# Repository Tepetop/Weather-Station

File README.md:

# Stacja pogodowa

Coś tu dopisze jeszcze

## AI coding harness

Lokalny agent Python do analizy i edycji kodu STM32, z automatyczną kompilacją
trzech wariantów projektu i testami hosta.

Instrukcja instalacji i przykłady: [tools/ai_harness/README.md](tools/ai_harness/README.md).

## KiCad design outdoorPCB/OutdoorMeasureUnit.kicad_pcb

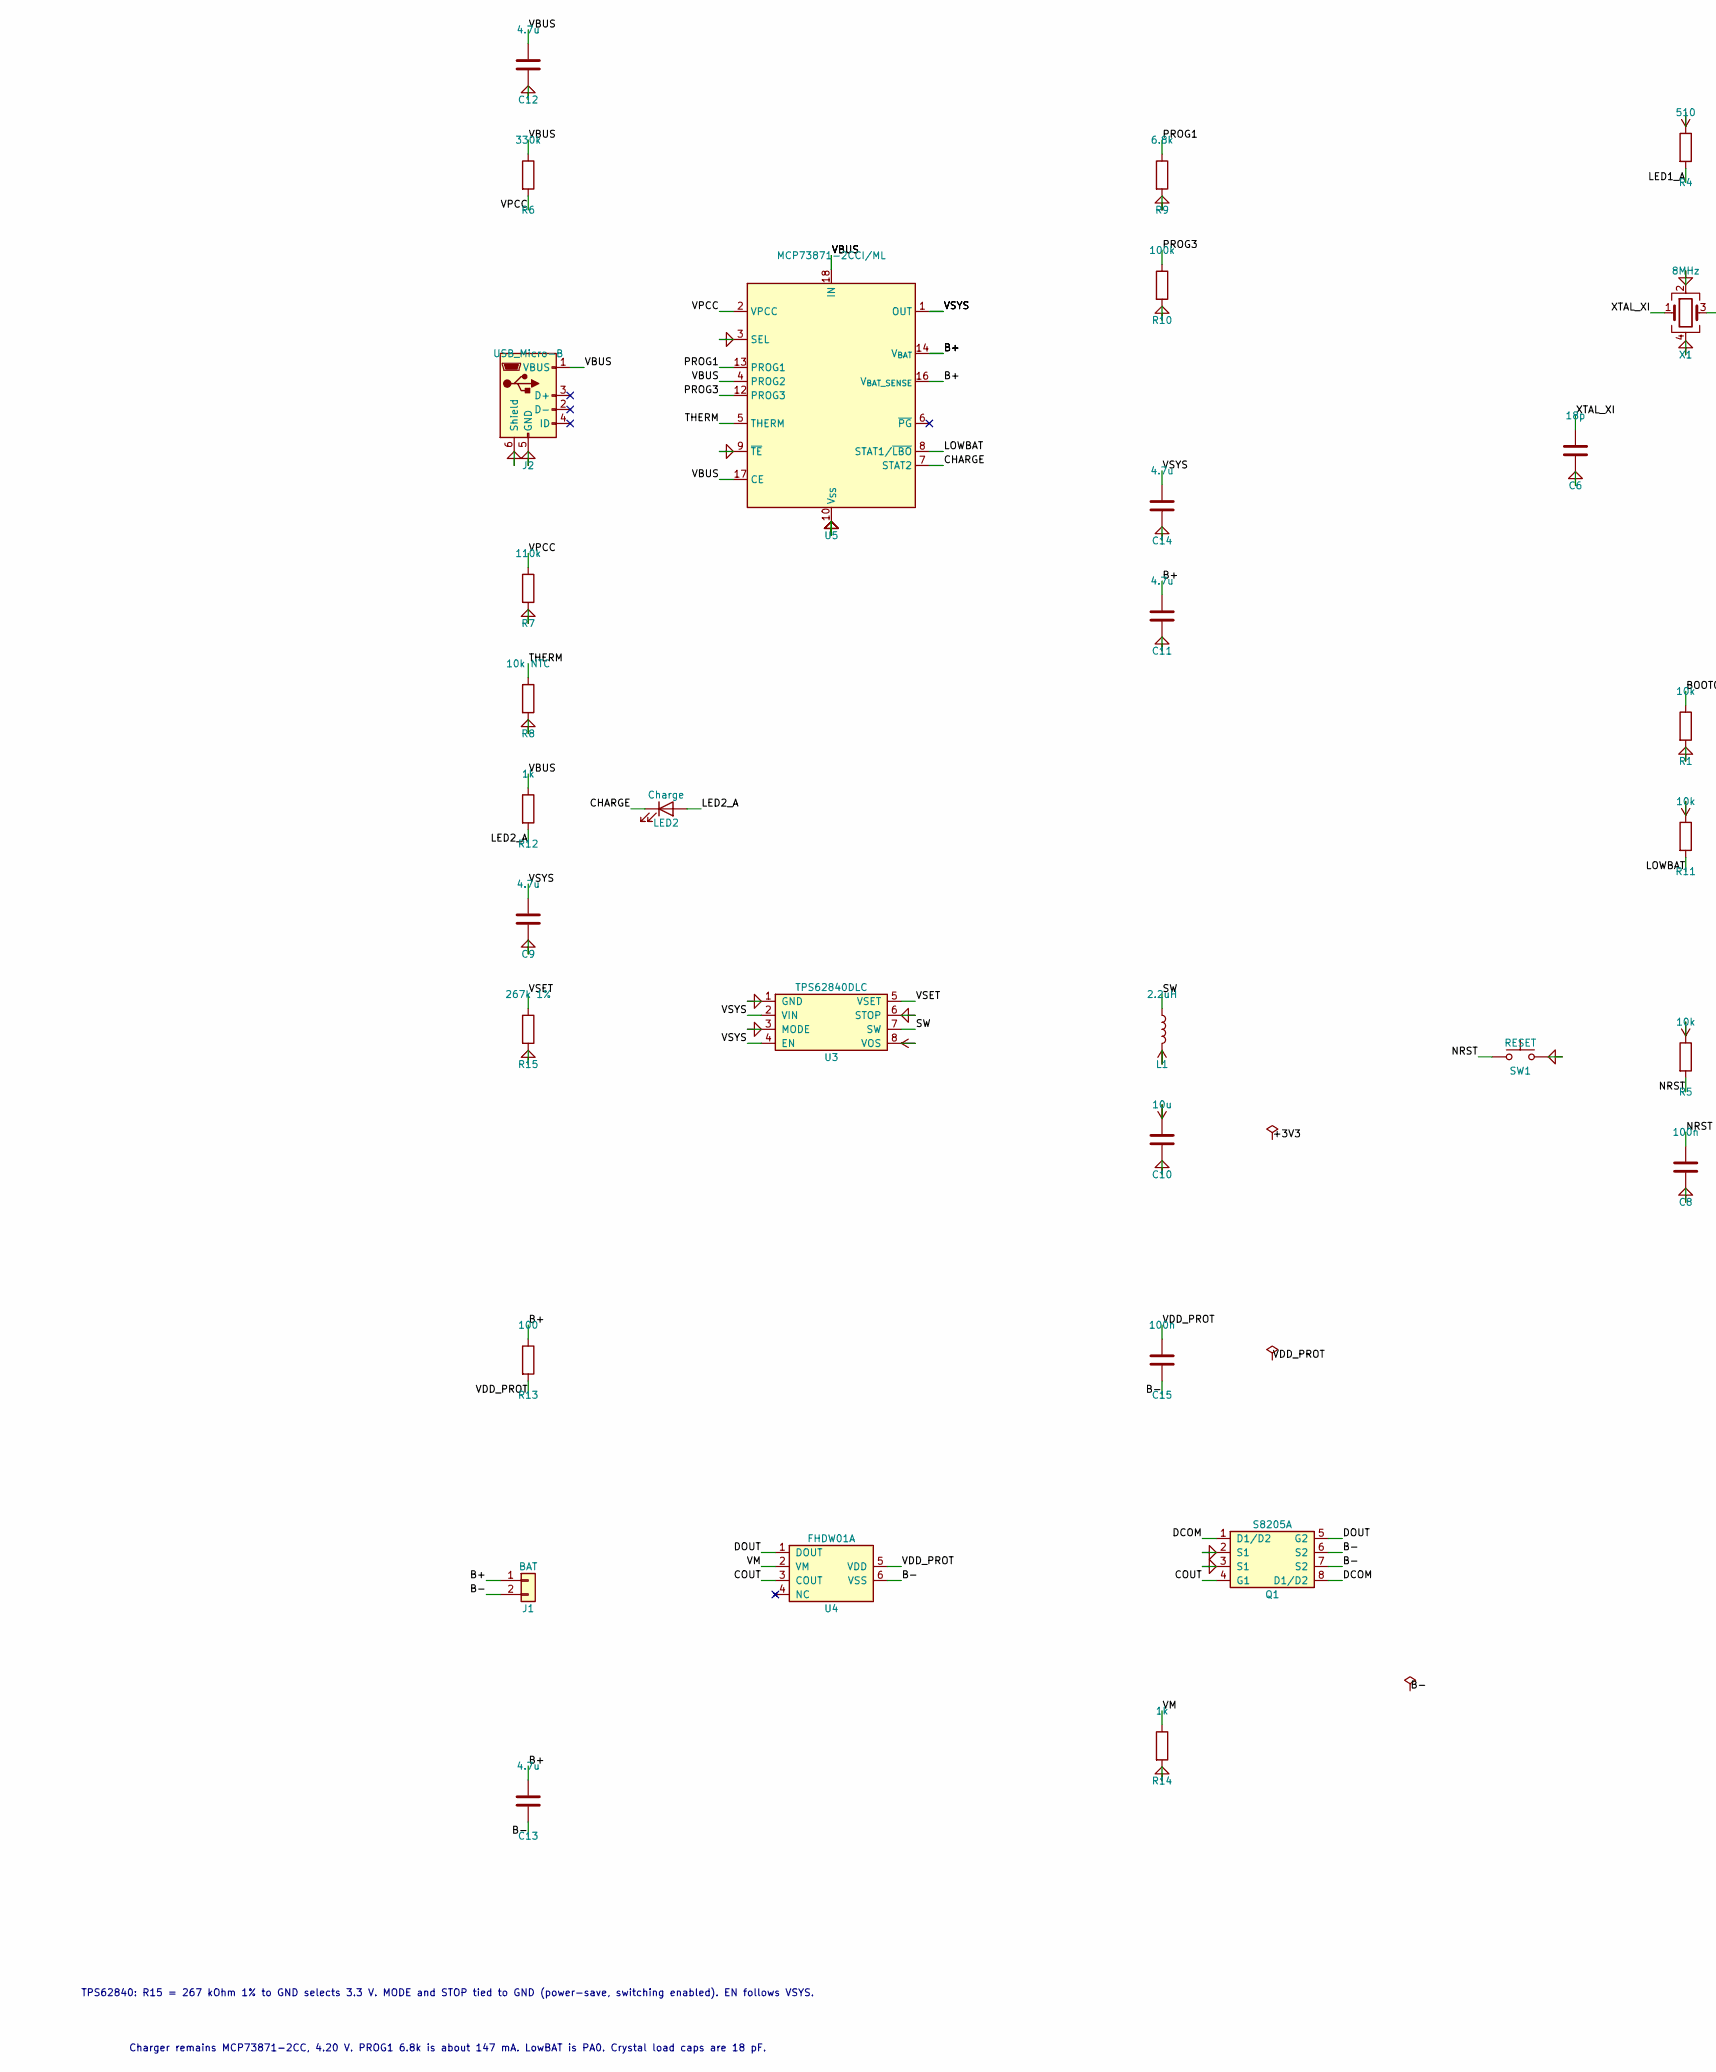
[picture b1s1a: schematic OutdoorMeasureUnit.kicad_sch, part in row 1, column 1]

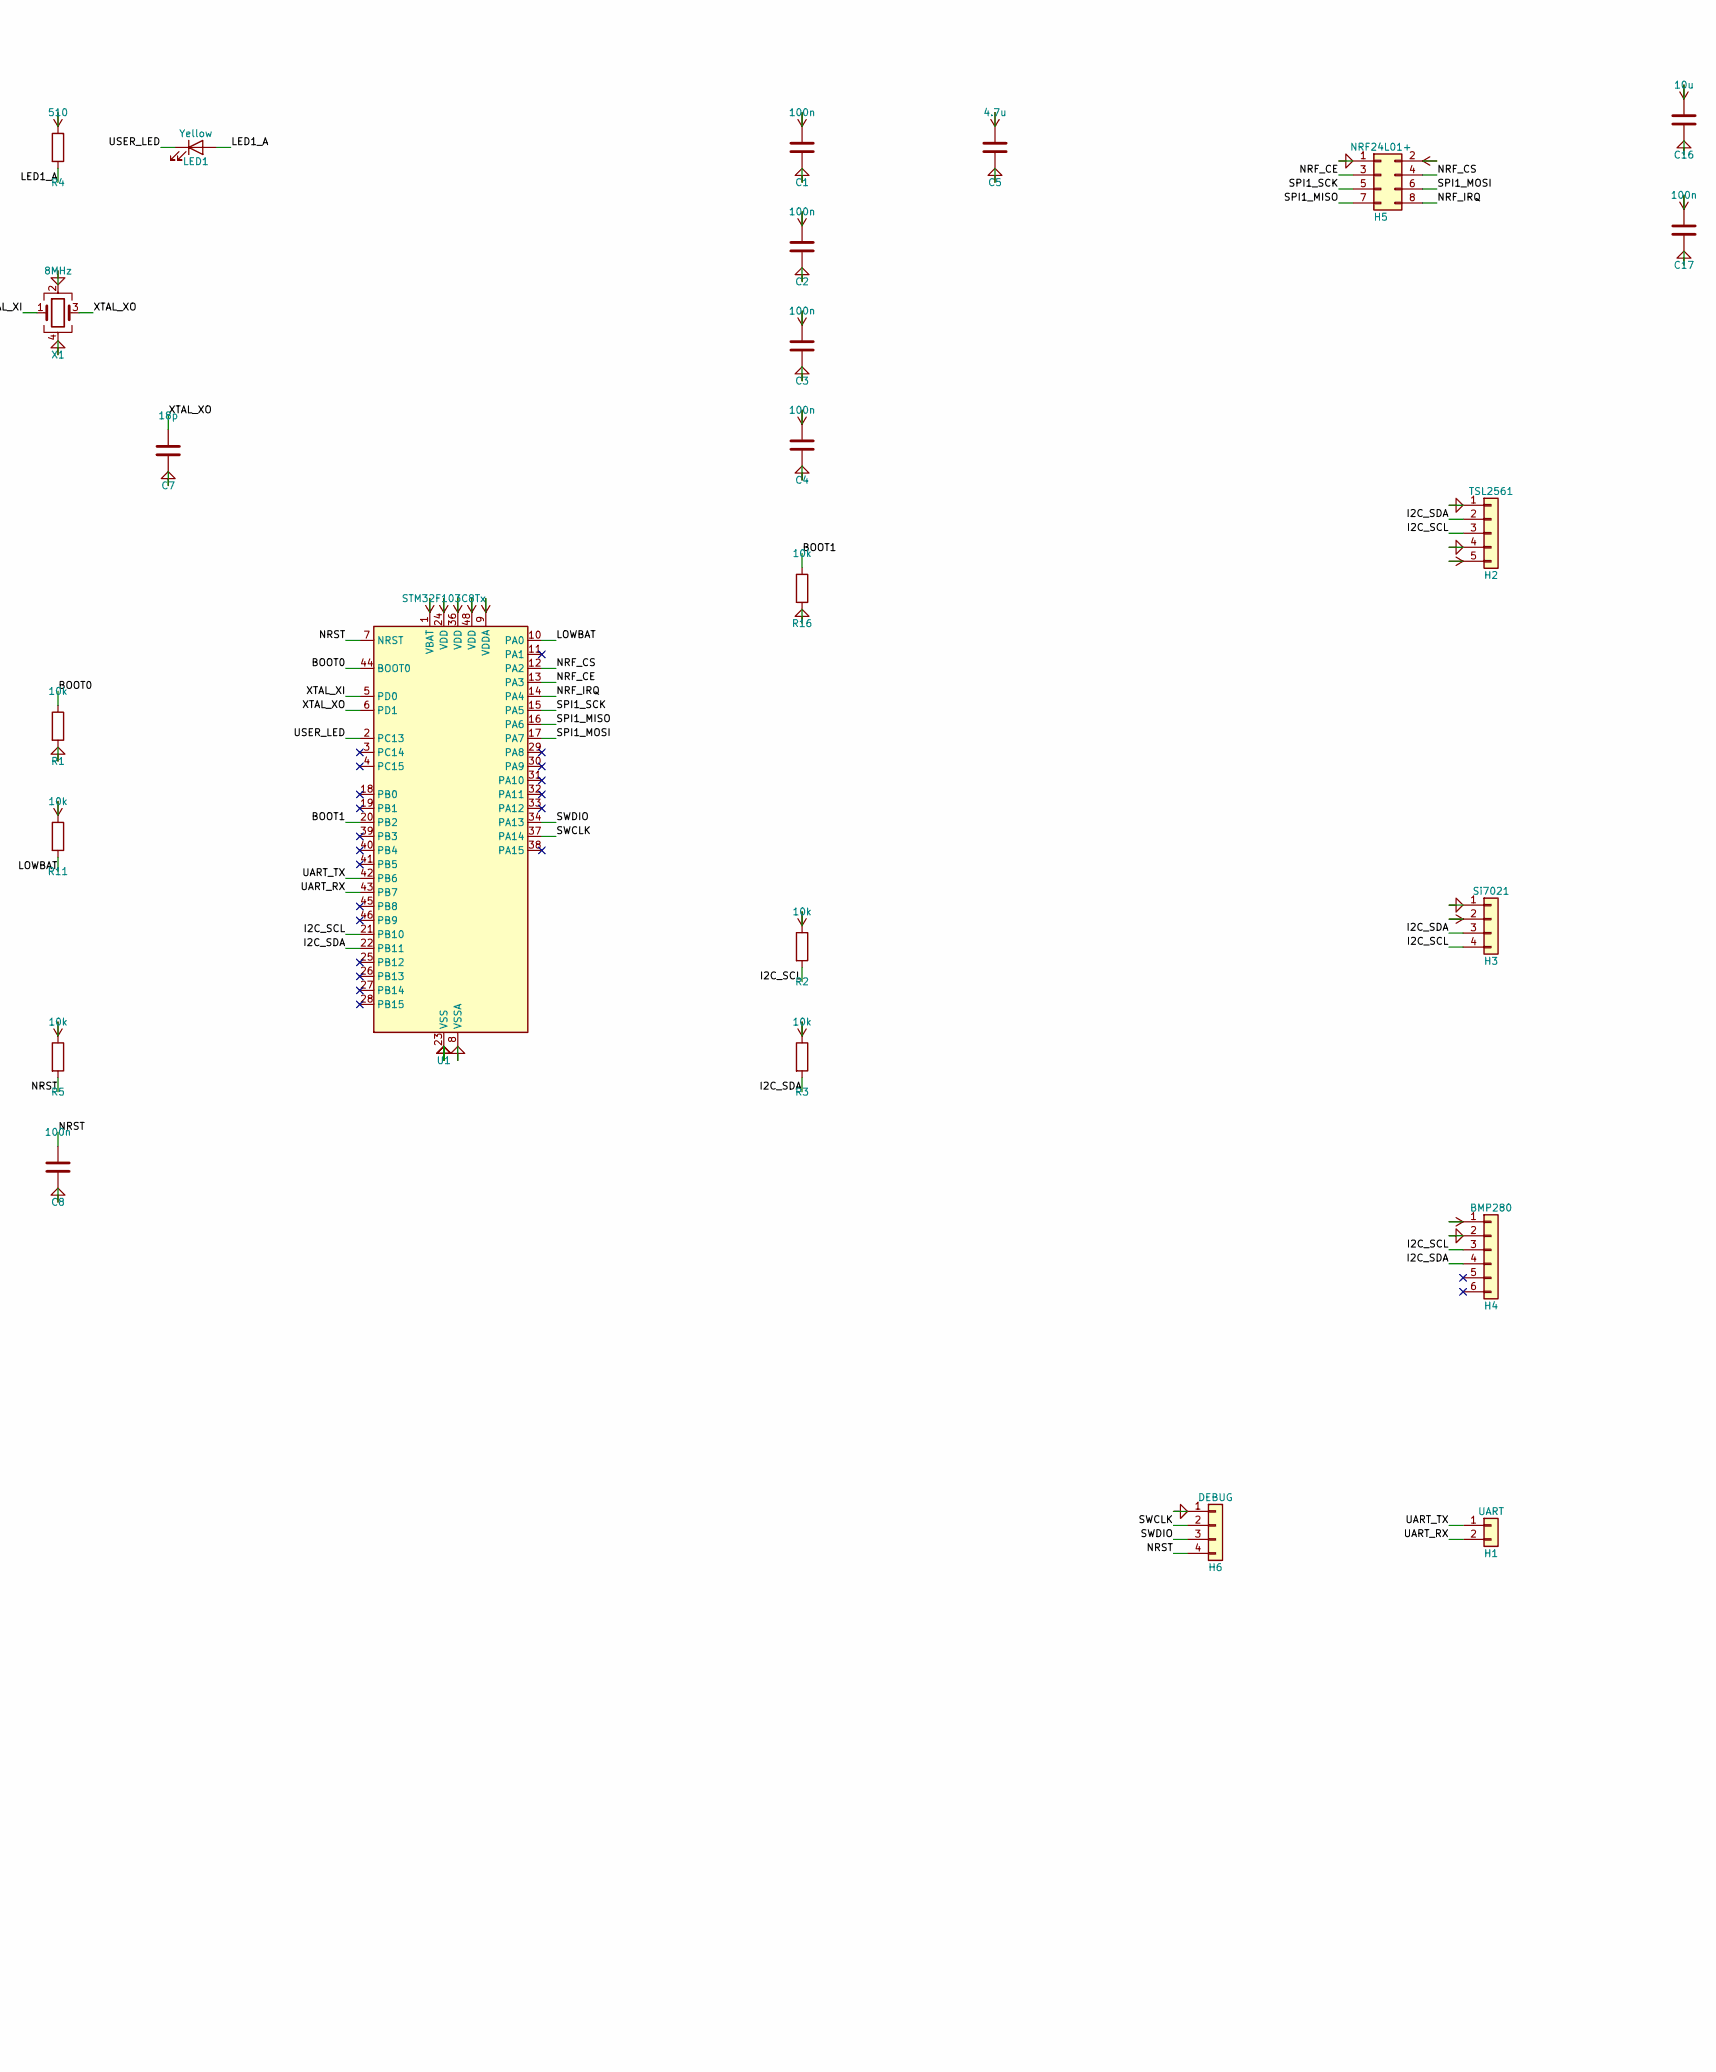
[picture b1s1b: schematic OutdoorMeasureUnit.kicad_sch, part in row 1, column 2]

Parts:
C1, C2, C3, C4, C8, C15, C17: 100n; C_0402_1005Metric
C5, C9, C11, C12, C13, C14: 4.7u; C_0603_1608Metric
C6, C7: 18p; C_0402_1005Metric
C10, C16: 10u; C_0603_1608Metric
H1: UART; PinHeader_1x02_P2.54mm_Vertical
H2: TSL2561; PinHeader_1x05_P2.54mm_Vertical
H3: Si7021; PinHeader_1x04_P2.54mm_Vertical
H4: BMP280; PinHeader_1x06_P2.54mm_Vertical
H5: NRF24L01+; PinHeader_2x04_P2.54mm_Vertical
H6: DEBUG; PinHeader_1x04_P2.54mm_Vertical
J1: BAT; JST_PH_B2B-PH-K_1x02_P2.00mm_Vertical
J2: USB_Micro-B; USB_Micro-B_Molex_47346-0001
L1: 2.2uH; L_Cenker_CKCS201610
LED1: Yellow; LED_0402_1005Metric
LED2: Charge; LED_0402_1005Metric
Q1: S8205A; TSSOP-8_4.4x3mm_P0.65mm
R1, R2, R3, R5, R11, R16: 10k; R_0402_1005Metric
R4: 510; R_0402_1005Metric
R6: 330k; R_0402_1005Metric
R7: 110k; R_0402_1005Metric
R8: 10k NTC; R_0402_1005Metric
R9: 6.8k; R_0402_1005Metric
R10: 100k; R_0402_1005Metric
R12, R14: 1k; R_0402_1005Metric
R13: 100; R_0402_1005Metric
R15: 267k 1%; R_0402_1005Metric
SW1: RESET; SW_SPST_B3U-1000P
U1: STM32F103C8Tx; LQFP-48_7x7mm_P0.5mm
U3: TPS62840DLC; Texas_VSON-HR-8_1.5x2mm_P0.5mm
U4: FHDW01A; SOT-23-6
U5: MCP73871-2CCI/ML; QFN-20-1EP_4x4mm_P0.5mm_EP2.5x2.5mm
X1: 8MHz; Crystal_SMD_3225-4Pin_3.2x2.5mm

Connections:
+3V3: C1.1, C2.1, C3.1, C4.1, C5.1, C10.1, C16.1, C17.1, H2.5, H3.2, H4.1, H5.2, L1.2, R2.1, R3.1, R4.1, R5.1, R11.1, U1.1 (VBAT), U1.9 (VDDA), U1.24 (VDD), U1.36 (VDD), U1.48 (VDD), U3.8 (VOS)
B+: C11.1, C13.1, J1.1, R13.1, U5.14 (V_{BAT}), U5.15 (V_{BAT}), U5.16 (V_{BAT_SENSE})
B-: C13.2, C15.2, J1.2, Q1.6 (S2), Q1.7 (S2), U4.6 (VSS)
BOOT0: R1.1, U1.44 (BOOT0)
BOOT1: R16.1, U1.20 (PB2)
CHARGE: LED2.1 (K), U5.7 (STAT2)
COUT: Q1.4 (G1), U4.3 (COUT)
DCOM: Q1.1 (D1/D2), Q1.8 (D1/D2)
DOUT: Q1.5 (G2), U4.1 (DOUT)
GND: C1.2, C2.2, C3.2, C4.2, C5.2, C6.2, C7.2, C8.2, C9.2, C10.2, C11.2, C12.2, C14.2, C16.2, C17.2, H2.1, H2.4, H3.1, H4.2, H5.1, H6.1, J2.5 (GND), J2.6 (Shield), Q1.2 (S1), Q1.3 (S1), R1.2, R7.2, R8.2, R9.2, R10.2, R14.2, R15.2, R16.2, SW1.2, U1.8 (VSSA), U1.23 (VSS), U1.35 (VSS), U1.47 (VSS), U3.1 (GND), U3.3 (MODE), U3.6 (STOP), U5.3 (SEL), U5.9 (~TE), U5.10 (V_{SS}), U5.11 (V_{SS}), U5.21 (V_{SS}), X1.2, X1.4
I2C_SCL: H2.3, H3.4, H4.3, R2.2, U1.21 (PB10)
I2C_SDA: H2.2, H3.3, H4.4, R3.2, U1.22 (PB11)
LED1_A: LED1.2 (A), R4.2
LED2_A: LED2.2 (A), R12.2
LOWBAT: R11.2, U1.10 (PA0), U5.8 (STAT1/~LBO)
NRF_CE: H5.3, U1.13 (PA3)
NRF_CS: H5.4, U1.12 (PA2)
NRF_IRQ: H5.8, U1.14 (PA4)
NRST: C8.1, H6.4, R5.2, SW1.1, U1.7 (NRST)
PROG1: R9.1, U5.13 (PROG1)
PROG3: R10.1, U5.12 (PROG3)
SPI1_MISO: H5.7, U1.16 (PA6)
SPI1_MOSI: H5.6, U1.17 (PA7)
SPI1_SCK: H5.5, U1.15 (PA5)
SW: L1.1, U3.7 (SW)
SWCLK: H6.2, U1.37 (PA14)
SWDIO: H6.3, U1.34 (PA13)
THERM: R8.1, U5.5 (THERM)
UART_RX: H1.2, U1.43 (PB7)
UART_TX: H1.1, U1.42 (PB6)
USER_LED: LED1.1 (K), U1.2 (PC13)
VBUS: C12.1, J2.1 (VBUS), R6.1, R12.1, U5.4 (PROG2), U5.17 (CE), U5.18 (IN), U5.19 (IN)
VDD_PROT: C15.1, R13.2, U4.5 (VDD)
VM: R14.1, U4.2 (VM)
VPCC: R6.2, R7.1, U5.2 (VPCC)
VSET: R15.1, U3.5 (VSET)
VSYS: C9.1, C14.1, U3.2 (VIN), U3.4 (EN), U5.1 (OUT), U5.20 (OUT)
XTAL_XI: C6.1, U1.5 (PD0), X1.1
XTAL_XO: C7.1, U1.6 (PD1), X1.3

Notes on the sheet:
TPS62840: R15 = 267 kOhm 1% to GND selects 3.3 V. MODE and STOP tied to GND (power-save, switching enabled). EN follows VSYS.
Charger remains MCP73871-2CC, 4.20 V. PROG1 6.8k is about 147 mA. LowBAT is PA0. Crystal load caps are 18 pF.

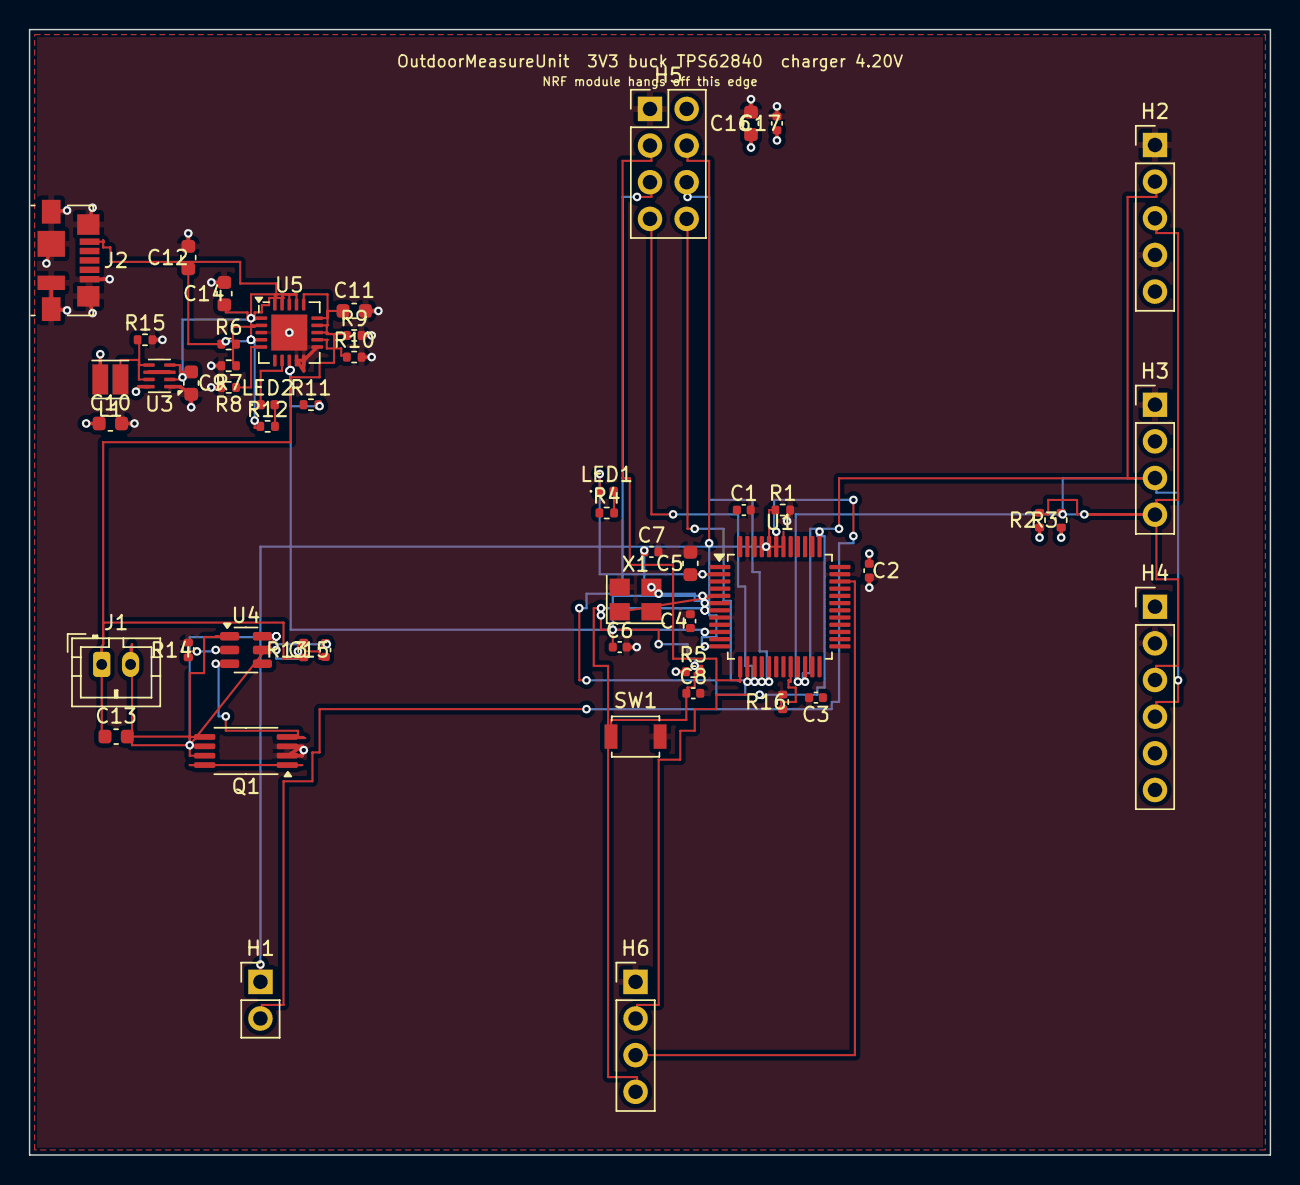
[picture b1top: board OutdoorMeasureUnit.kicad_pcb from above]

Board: 4 copper layers, 86.0 x 78.0 mm, 51 parts (0 on the bottom side), 39 nets.

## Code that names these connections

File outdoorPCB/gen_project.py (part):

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            "    (comment 1 \"STM32F103 weather station. Charge stays at 4.20 V (MCP73871-2CC).\")",
            "    (comment 2 \"3.3 V from TPS62840 buck, input is charger OUT. R15 267k sets 3.3 V.\")",
            "    (comment 3 \"Crystal load caps are 18 pF; change them to match the crystal CL.\")",
            "    (comment 4 \"LowBAT is PA0 (WKUP), matching the EasyEDA schematic. FHDW01A lock is 4.28 V.\")",
            "  )",
            "  (lib_symbols",
        ]
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            "    (effects (font (size 1.27 1.27)))\n"
            "    (uuid %s))" % uid())
        chunks.append(
            '  (text "Charger remains MCP73871-2CC, 4.20 V. PROG1 6.8k is about 147 mA. LowBAT is PA0. Crystal load caps are 18 pF." (at 25.4 395 0)\n'
            "    (effects (font (size 1.27 1.27)))\n"
            "    (uuid %s))" % uid())
        chunks.append('  (sheet_instances (path "/" (page "1")))')
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    mcu_nets = {
        "VBAT": "+3V3", "VDDA": "+3V3", "VDD": "+3V3",
        "VSSA": "GND", "VSS": "GND",
        "PD0": "XTAL_XI", "PD1": "XTAL_XO", "NRST": "NRST",
        "PC13": "USER_LED", "PA0": "LOWBAT",
        "PA2": "NRF_CS", "PA3": "NRF_CE", "PA4": "NRF_IRQ",
        "PA5": "SPI1_SCK", "PA6": "SPI1_MISO", "PA7": "SPI1_MOSI",
        "PB2": "BOOT1", "BOOT0": "BOOT0",
        "PB6": "UART_TX", "PB7": "UART_RX",
        "PB10": "I2C_SCL", "PB11": "I2C_SDA",
        "PA13": "SWDIO", "PA14": "SWCLK",
    }
    if mcu_nets["PA0"] != "LOWBAT":
        raise SystemExit("LOWBAT must stay on PA0 (WKUP), as on the EasyEDA sheet")
    stm_pins = {}
    for pin in pins_of(stm):
        if pin["name"] in mcu_nets:
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
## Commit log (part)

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2025-09-15 create project
2025-09-15 Create outdoor project
2025-09-15 Outdoor: Add nessesary files and sensors library
2026-01-19 Add measurement module for Outdoor unit
    Created measurement.c and measurement.h in Outdoor unit/Core to handle
    sensor measurements from si7021, bmp280, and TSL2561 using a state
    machine. Added support for returning measurement data in CSV format.
2026-01-19 Refine measurement module with RUN state and explicit IDLE trigger
    Updated the measurement module to include MEAS_STATE_RUN for starting
    the measurement cycle. MEAS_STATE_IDLE now waits for an external trigger
    via Measurement_Start(). The state machine returns to IDLE after a successful
    cycle.
2026-01-20 Zmiana projektu na VSCode z CMake
2026-01-20 Porządki w projekcie VSCode dla outdoor_unit
2026-01-21 Set default configuration for BMP280 sensor
2026-01-21 Refactor measurement module to use device state
2026-01-21 Refactor measurement module state management
2026-01-22 Massive changes in code. Succesfully migrated project from cubeide to vscode. All sensors are working but i have to check if values are correct.
2026-01-22 Removed old folder which were created for stmcubeide
2026-01-22 Fixed file naming
2026-01-22 Fixed group measurement library and added it to main loop
2026-01-22 Clean up
2026-01-25 Added DMA support and fixed BMP280 driver
2026-01-25 BMP280 is working with dma fine
2026-01-27 Improve measurements state machine
2026-01-27 FIxed error in TSL2561
2026-01-28 Upgraded comments in TSL2561.c for better clarity
2026-01-28 Translate si7021 description
2026-01-30 Create Indoor Unit project structure and initial files
2026-01-30 LCD connected, no errors in files but lcd not displaying anything.
2026-01-30 Still nothing displayed on the LCD
2026-02-01 Massive changes in PCD8544 library. LCD is finnaly working. Changed internal structure of the library
2026-02-01 Improve menu navigation and add new features. Created menu example in main which icnliude scorlling through menu items and selecting them.
2026-02-05 Added new files for ds3231 and i2c, modified existing files to integrate the new functionality, and updated the project configuration accordingly.
2026-02-11 Completed DS3231 library (pariatlly)
2026-02-11 Added encoder compatibility. Now if user enters submenu, there will be additional "POWROT" option and also menu/submenu name will be displayed on the top of the screen.
2026-02-11 Added ecnoder library. Updated main.c to initialize encoder and LCD, and added a soft timer for LED toggling. Updated menu context and LCD instance declarations.
2026-02-11 Cmake changes
2026-02-11 Again cmake update
2026-02-12 Encoder is workingm IRQ form button and timers properly navigate throught menu
2026-02-12 Now its possible to show detail of submenus if PCD8544_SHOW_DETAILS is enabled in PCD8544_config.h
2026-02-12 Adde support for IRQ in button debounce library. Succesfully integrated the buton debounce library into the main application and tested it with the encoder button.
2026-02-12 Added drawing file which contains functions for drawing lines and circles on the PCD8544 LCD. Updated main.c to include the drawing header and added a demo to draw a circle and lines on the LCD. Upda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
2026-02-16 Stworzono pierwszą wersje menu pomiarów i statusu Dodano symulacje pomiarów
2026-02-17 Dodano opcje rysowania wykresu z dwoma trybami Dane prawidłow są aktualizowane na ekranie Menu działa poprawnie, można przełączać się między wykresami i menu
2026-02-20 Fixed wrapiing issue when x or y is 0
2026-02-21 First take to fix encoder bug
2026-02-21 Fiex encoder deadzone at dir change
2026-02-22 Udało się dodać dwie nowe trzcionki na bazie sterownika SSD1306
2026-02-22 I chuj ekran nie działa
2026-02-22 DS3231 działa prawidłowo, czas jest pobierany i aktualzowany.
2026-02-22 Setup B0 pin for IRQ from DS3231
2026-02-22 DS3231 IRQ not working
2026-02-22 DS3231 library is working.
2026-02-22 Test agenta planera
2026-02-22 Testuje inna libke od ds3231, dodaje skille do AI
2026-02-24 Added two DS3231 librarier. IDK which one ill use
2026-02-26 Changes inside IRQ flags functions
2026-02-26 Added nrf24l01 library.
2026-02-26 Added pdf skill, refactored nrfl24 code.
2026-02-26 Added SPI2 pins configuration for NRF24L01
2026-03-04 Ja juz nie wiem co tu sie odpierdala.# Please enter the commit message for your changes. Lines starting
2026-03-05 Naprawiono działanie BMP280, trzeba było dodać połączenie pomiedzy SDO i masa/zasilanie w celu ustalenia adresu
2026-03-06 Stacja pomiarowa i centralna działają prawidłowo, dane są wyświetlane na LCD, pomiary wykonywane są co 3 sekundy
2026-03-06 Stacja pomiarowa i centralna działaja, dane sa wyświetlane na LCD,
2026-03-08 Dzialajaca wersja podstawowa stacji pogodowej dla jednostki wewnętrznej Brakuje tylko zapisu danych pomiarowych do pamięci zewnętrznej (SD)
2026-03-08 Zaktualizowano bibileke, dodano manualne ustawienie czasu przy starcie, dodano wykres swiatla,
2026-03-08 First cleanup of outdoor unit code. Added new header file for measurement unit configuration.
2026-03-08 Zrefaktoryzowano main i measurement.c, dodano measurement_unit_config. Poprawiono przepływ danych, wykasowano flage linkera od float po uart
2026-03-10 Zmienienio ramke wysylanych danych, dodano stan czujników. Dodano maszyne stanów do pomiarów
2026-03-10 Zmieniono sposób realizacji opcji powrotu do poprzedniego MENU. Dodano lepsza reprezentace statnu stacji pomiarowej.
2026-03-13 Poprawiono odświeżanie danych w wiodku wykresu i statusu
2026-03-13 Dodano funckje rysujacą napis wycentrowany względem szerokości ekranu
2026-03-13 Dodano UART do projektu. Nowa opcja screensaver, która sie wlacza po 30 sekundach bezczynności. Jednak nie działa do końca tak jak bym tego chciał
2026-03-16 Poprawiono obsługe screen saver, stanu debounce przy przerwaniu od przycisku
2026-03-17 Poprwka błędów, dodano lepsza obsluge bledow z logowaniem na uart przy aktywnej fladze
2026-03-17 Dodano IWDG, dalszy refactor kodu z main do zewnetrzynch plików.
2026-03-17 Zmiana przypisania wartosci error code do data.sensorStatus Jedna zmienna o stanie czujnikow jest zbedna ale narazie zostawiam
2026-03-17 Zmiany w sposobie wyswietlania statusu bledow, chyba zrobie tak, ze po dwa wiersze beda na jedna stacje
2026-03-17 Refactor bibliteki nrf24l01
2026-03-29 Dodano rozszerzone logi debugowania w pliku debug_log.c, ogólnie układy działają i problem polega na slabych połączeniach(obecnie płytka stykowa + kabelki)
2026-04-28 Dodano nowy folder z kodem do pi pico W, zawierajacy serwer reperzentujacy dane pomiarowe. PIco W działa jako dashboard
2026-04-28 Dodano funkcje formatujaca dane pomiarowe do postaci CSV dla pico W wysylane po UART. Nie testowano
2026-04-28 zmiana nazwy glonwego pliku .py
2026-04-29 Dodano wyłączenie IWDG podczas debugowania, aby uniknąć resetu systemu podczas zatrzymania CPU przez debugger.
2026-05-07 proba naprawy NRF TX Timeout, dodano jaki mechanizm ponownej inicjalizacji ale po udanym reinicie dalej jest blad TX lub RX timeout
2026-05-07 Aktualizacja obłsugi stacji pogodowej. Wydzielono UI i logikę do osobnych plików
2026-05-09 serwer nie dziala w obecnym folderze, musze go odpalac z innego pliku. Potem sie to ogarnie. Stacja dziala prawidlowo po zmianach
2026-05-10 Ponowne wklejeniu folderu z microserwerem, dalej nie dziala. Dodano nowa opcje w menu Ustaw RTC/, teaz mozna z poziomu LCD ustawic bierzacy czas i date
2026-05-18 Jak zwykle pelno zmian, w wielu plikach. Generalnie zmienilem troche oblsuge menu, aj aj dodal status stacji centralnej. Wprowqadzono tez zmiany zwiazane z cmake
2026-05-18 chuj wie co szczerze xD
